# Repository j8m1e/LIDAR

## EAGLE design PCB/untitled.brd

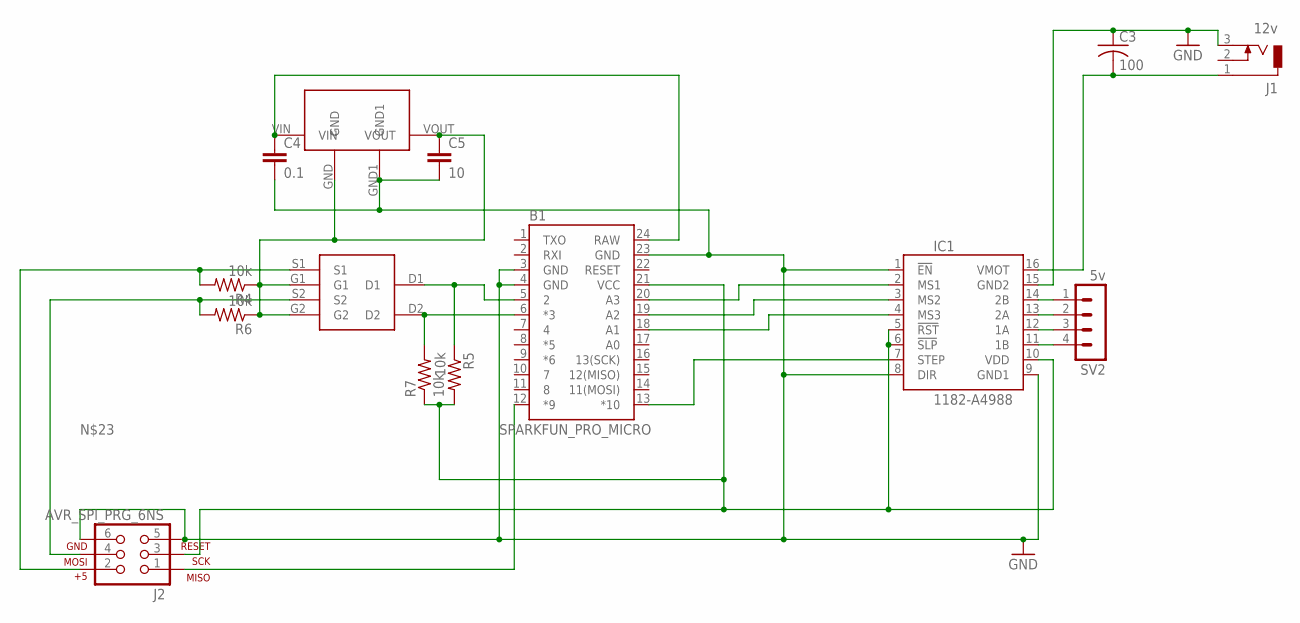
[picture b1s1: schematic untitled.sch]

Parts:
B1: SPARKFUN_PRO_MICRO
C3: 100; C050-075X075
C4: 0.1; 0603-CAP
C5: 10; 0603-CAP
IC1: 1182-A4988; A4988
J1: 12v; DCJ0303
J2: AVR_SPI_PRG_6NS; 2X3-NS
R4, R5, R6, R7: 10k; 0207/10
SV2: 5v; MA04-1
U$2: LD1117; SOT223
U$3: BSS138; SOT363

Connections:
GND: B1.3 (GND), B1.4 (GND), B1.23 (GND), C3.1, C4.2, C5.2, IC1.1 (!EN), IC1.8 (DIR), IC1.9 (GND1), IC1.15 (GND2), J1.3, J2.5, J2.6, U$2.GND1
unnamed: IC1.14 (2B), SV2.1
unnamed: C5.1, R4.1, R6.1, U$2.GND, U$2.VOUT, U$3.G1, U$3.G2
unnamed: IC1.13 (2A), SV2.2
unnamed: IC1.12 (1A), SV2.3
unnamed: IC1.11 (1B), SV2.4
unnamed: B1.20 (A3), IC1.2 (MS1)
unnamed: B1.19 (A2), IC1.3 (MS2)
unnamed: B1.18 (A1), IC1.4 (MS3)
unnamed: B1.21 (VCC), IC1.5 (!RST), IC1.6 (!SLP), IC1.10 (VDD), J2.3, R5.2, R7.1
unnamed: C3.2, IC1.16 (VMOT), J1.1
unnamed: B1.13 (*10), IC1.7 (STEP)
unnamed: B1.24 (RAW), C4.1, U$2.VIN
unnamed: B1.12 (*9), J2.1
unnamed: B1.5 (2), R5.1, U$3.D1
unnamed: B1.6 (*3), R7.2, U$3.D2
unnamed: J2.2, R4.2, U$3.S1
unnamed: J2.4, R6.2, U$3.S2

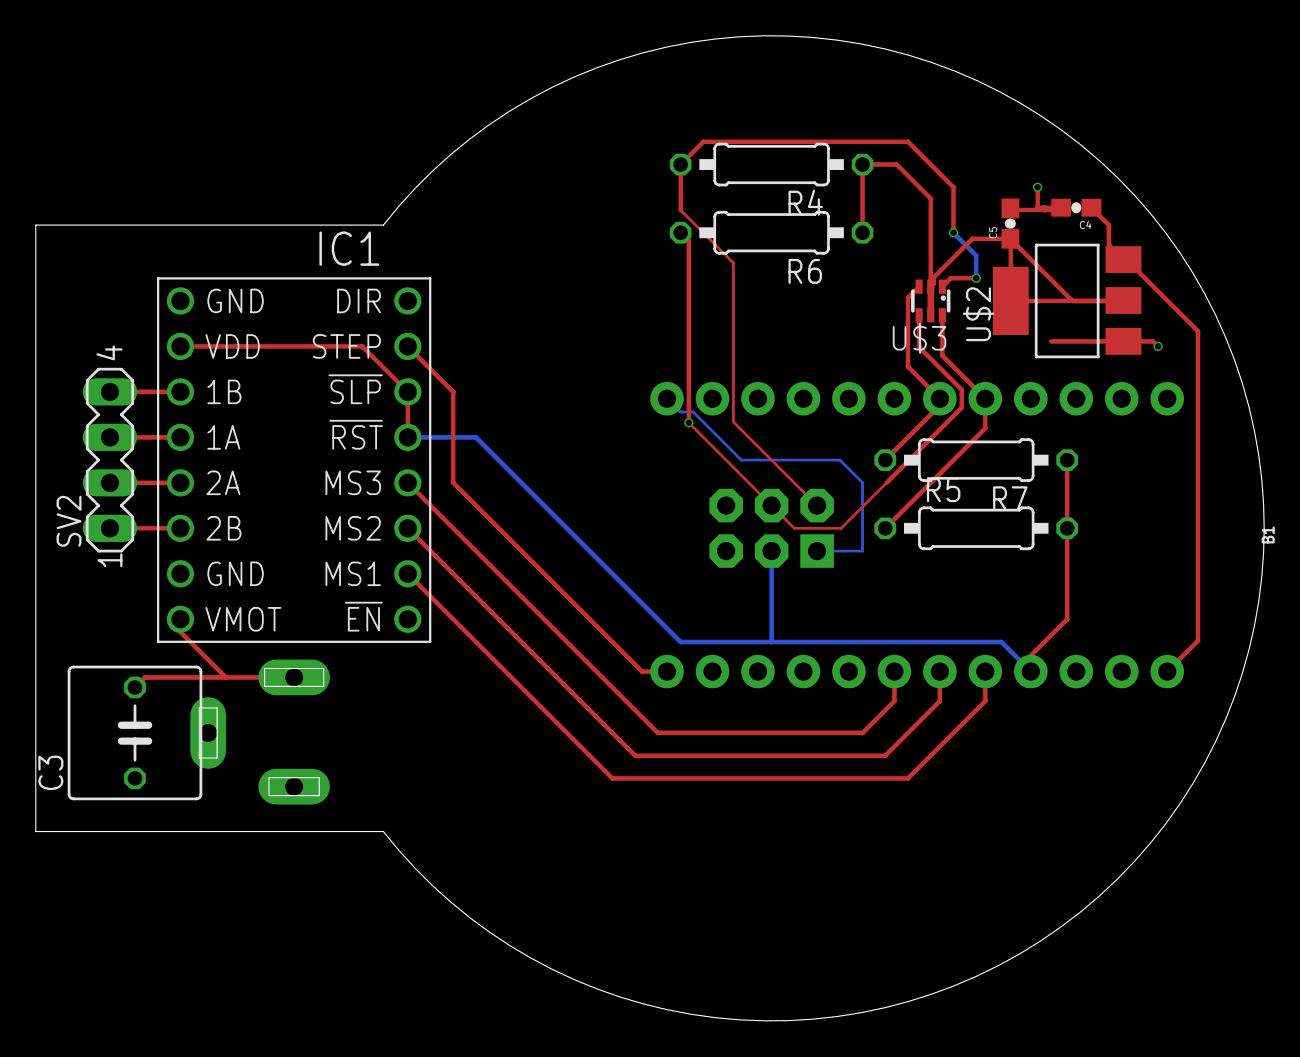
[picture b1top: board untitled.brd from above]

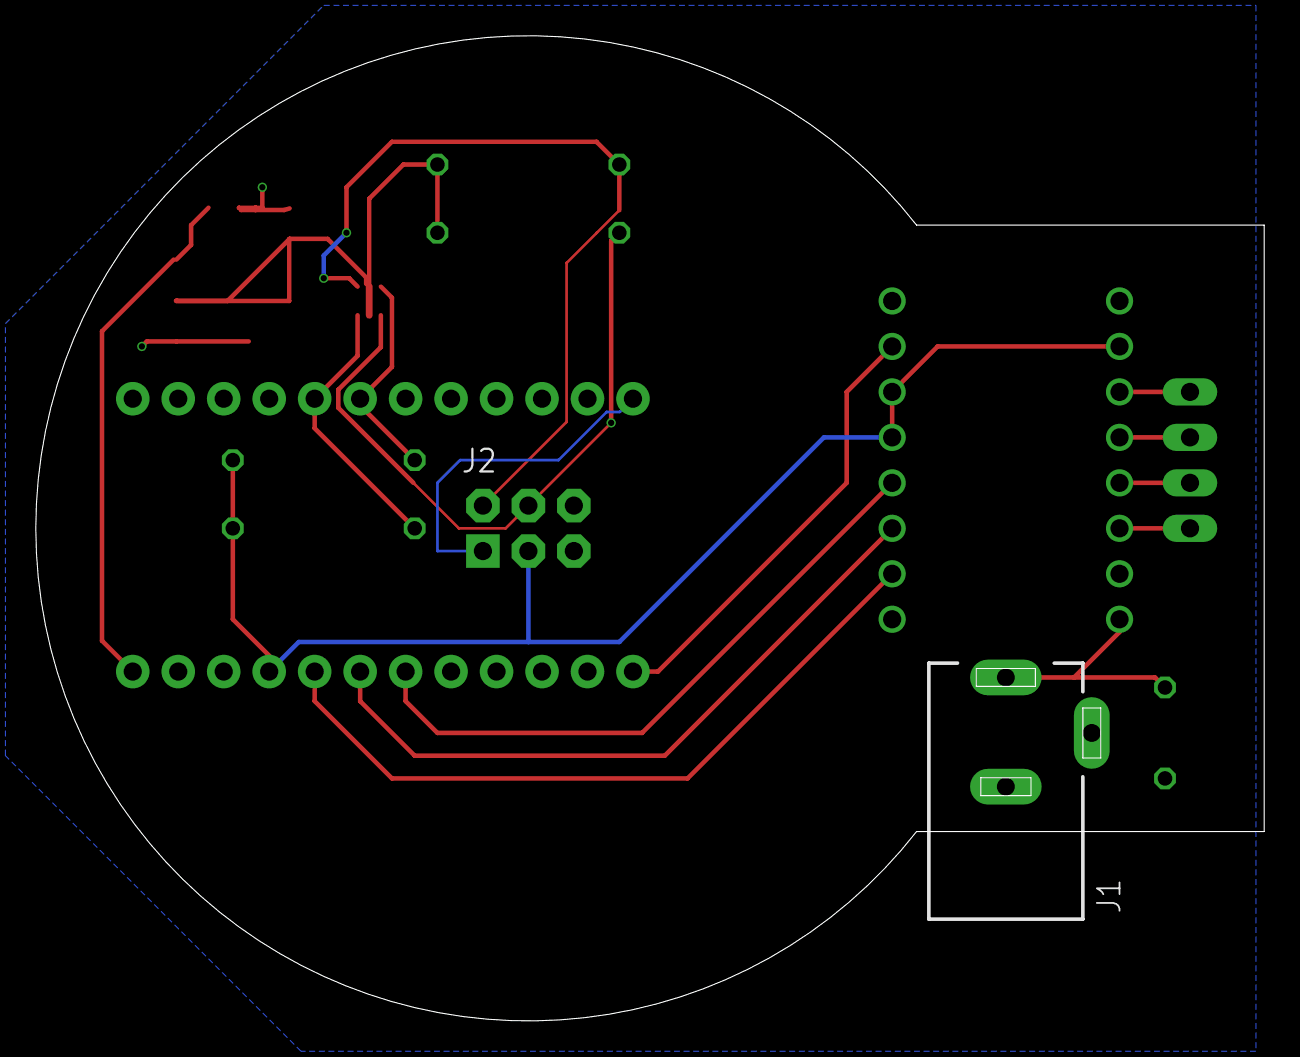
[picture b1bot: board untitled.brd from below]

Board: 2 copper layers, 68.6 x 55.0 mm, 14 parts (2 on the bottom side), 18 nets.

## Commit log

2024-08-10 "updated ./lidarang.las"
2024-08-10 "updated ./TFLuna-I2C-master/README.md"
2024-08-10 "updated ./lidar.ino"
2024-08-10 "updated ./Untitled.ipynb"
2024-08-10 "updated ./TFLuna-I2C-master/library.properties"
2024-08-10 "updated ./lidar.ipynb"
2024-08-10 "updated ./TFLuna-I2C-master/tfluna/TFLI2C.cpp"
2024-08-10 "updated ./lasvalidate.log"
2024-08-10 "updated ./lidarcar.las"
2024-08-10 "updated ./TFLuna-I2C-master/keywords.txt"
2024-08-10 "updated ./TFLuna-I2C-master/example/TFLI2C_simple.ino"
2024-08-10 "updated ./TFLuna-I2C-master/example/TFLI2C_example.ino"
2024-08-10 "updated ./TFLuna-I2C-master/documents/TF-luna-A03 Datasheet.pdf"
2024-08-10 "updated ./TFLuna-I2C-master/documents/TF-Luna A01 Product Manual.pdf"
2024-08-10 "updated ./data/DS1Z_QuickPrint3.png"
2024-08-10 "updated ./data/DS1Z_QuickPrint5.png"
2024-08-10 "updated ./data/DS1Z_QuickPrint1.png"
2024-08-10 "updated ./data/DS1Z_QuickPrint2.png"
2024-08-10 "updated ./TFLuna-I2C-master/tfluna/TFLI2C.h"
2024-08-10 "updated ./data/DS1Z_QuickPrint4.png"
2024-08-10 "updated ./TFLuna-I2C-master/documents/TF-Luna A03 Product Manual.pdf"
2024-08-10 "updated ./data/DS1Z_QuickPrint9.png"
2024-08-10 "updated ./data/DS1Z_QuickPrint7.png"
2024-08-16 "updated ./PCB/untitled.b#5"
2024-08-16 "updated ./PCB/untitled_2021-04-06.zip"
2024-08-16 "updated ./PCB/untitled.cam"
2024-08-16 "updated ./PCB/dxfimp.scr"
2024-08-16 "updated ./PCB/untitled.brd"
2024-08-16 "updated ./PCB/untitled.b#4"
2024-08-16 "updated ./PCB/BSS138.lbr"
2024-08-16 "updated ./PCB/untitled.b#3"
2024-08-16 "updated ./PCB/untitled.b#2"
2024-08-16 "updated ./PCB/untitled.s#4"
2024-08-16 "updated ./PCB/untitled.s#5"
2024-08-16 "updated ./PCB/eagle.epf"
2024-08-16 "updated ./PCB/untitled.s#3"
2024-08-16 "updated ./PCB/untitled.b##"
2024-08-16 "updated ./PCB/untitled.s#2"
2024-08-16 "updated ./PCB/atmega32u4.lbr"
2024-08-16 "updated ./PCB/untitled.b#9"
2024-08-16 "updated ./PCB/untitled.pro"
2024-08-16 "updated ./PCB/SparkFun.lbr"
2024-08-16 "updated ./PCB/A4988.l#1"
2024-08-16 "updated ./PCB/untitled.b#7"
2024-08-16 "updated ./PCB/A4988.l#3"
2024-08-16 "updated ./PCB/untitled_01.job"
2024-08-16 "updated ./PCB/untitled_03.job"
2024-08-16 "updated ./PCB/untitled.b#8"
2024-08-16 "updated ./PCB/BSS138.l#1"
2024-08-16 "updated ./PCB/untitled_00.job"
2024-08-16 "updated ./PCB/untitled.b#6"
2024-08-16 "updated ./PCB/untitled_02.job"
2024-08-16 "updated ./PCB/untitled.s#9"
2024-08-16 "updated ./PCB/untitled.b#1"
2024-08-16 "updated ./PCB/untitled.s#7"
2024-08-16 "updated ./PCB/CAMOutputs/GerberFiles/solderpaste_top.gbr"
2024-08-16 "updated ./PCB/CAMOutputs/GerberFiles/silkscreen_top.gbr"
2024-08-16 "updated ./PCB/CAMOutputs/GerberFiles/copper_bottom.gbr"
2024-08-16 "updated ./PCB/untitled.sch"
2024-08-16 "updated ./PCB/LD1117.lbr"
2024-08-16 "updated ./PCB/A4988.l#2"
2024-08-16 "updated ./PCB/untitled.s#6"
2024-08-16 "updated ./PCB/untitled_04.job"
2024-08-16 "updated ./PCB/untitled.s#8"
2024-08-16 "updated ./PCB/untitled.s#1"
2024-08-16 "updated ./PCB/CAMOutputs/GerberFiles/gerber_job.gbrjob"
2024-08-16 "updated ./PCB/CAMOutputs/GerberFiles/soldermask_bottom.gbr"
2024-08-16 "updated ./PCB/CAMOutputs/DrillFiles/drill_1_16.xln"
2024-08-16 "updated ./PCB/CAMOutputs/Assembly/PnP_untitled_front.txt"
2024-08-16 "updated ./PCB/CAMOutputs/GerberFiles/copper_top.gbr"
2024-08-16 "updated ./PCB/CAMOutputs/Assembly/untitled.txt"
2024-08-16 "updated ./PCB/CAMOutputs/GerberFiles/soldermask_top.gbr"
2024-08-16 "updated ./PCB/CAMOutputs/GerberFiles/profile.gbr"
2024-08-16 "updated ./PCB/CAMOutputs/GerberFiles/solderpaste_bottom.gbr"
2024-08-16 "updated ./PCB/CAMOutputs/GerberFiles/silkscreen_bottom.gbr"
2024-08-16 "updated ./PCB/CAMOutputs/Assembly/PnP_untitled_back.txt"

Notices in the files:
parts and their libraries:
SparkFun-Boards: Licensing: Creative Commons ShareAlike 4.0 International - https://creativecommons.org/licenses/by-sa/4.0
SparkFun: Licensing: CC v3.0 Share-Alike You are welcome to use this library for commercial purposes.
